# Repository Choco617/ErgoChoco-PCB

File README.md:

# ErgoChoco-PCB
 My first PCB - a de-split split layout taking my favorite design details from the Corne, Kyria, Absolem, and others.

## The name
 I'm an engineer, and true to form I'm bad at naming things. I'd heard the ErgoDox was designed by a user named Dox, and my handle is Choco617, so: ErgoChoco.
 
## Layout explanation:
I love my Corne, but I quickly found that I always orient the halves the same way, making the actual separation and the TRRS cable more of a nuisance, much as I love the concept. So I experimented with angles and settled on 30°. I had also always wondered if I would like more columnar stagger: the Corne seems pretty conservative on that. So after reading the Kyria design log, I took the same approach, made some measurements of my own fingers’ natural resting positions, and discovered they were negligibly different from the Kyria’s, so I lifted those columnar stagger dimensions wholesale. I love the look of the 1.5U thumb keys on the Corne, but I admit it’s always been annoying for keycap compatibility that they prevent me from just getting a Planck set, so I replaced the 1.5U keys with 1U. I set the hands just far enough apart to fit a Pro Micro between them. A cardboard prototype with leftover switches/caps stuffed into it confirmed that was a comfy layout for me (and the all-1U thumb arcs don’t look as bad as I worried they would).

## Design Priorities:

### PCB
- Kailh hotswap sockets (direct soldering not supported: I'm the only intended user, so I can do what I want :P)
- In-switch LED (with Holtites so that it doesn't defeat the purpose of switch hotswap)
- South-facing switches (I like seeing the LEDs right up front)
- Pro Micro. I originally designed this with an onboard MCU, then decided I would rather keep all the complicated stuff on a Pro Micro to keep the PCB simpler/cheaper and allow me to replace the controller if something awful happened. Also, Pro Micro instead of Elite-C just because I already have micro-USB cables. The Pro Micro is socketed anyway, so I can always change later if I feel like it.
- SMD all the things (mostly diodes/resistors). I wanted to see if I could actually solder all of it myself, and I like the idea of keeping everything as small as possible, and technically minimizing EMI.
- Ground plane everywhere. My original Contra was very prone to ESD shocks, so in the original onboard-MCU version of this PCB, I had an ESD protection circuit with a PRTR5V0U2X. Now with a Pro Micro design, the best I can do (I think) is extensive ground planes and connecting the mounting holes to them so the PCB is grounded to the stainless steel case. I'm a mechanical engineer, not an electrical engineer, so I hope this is sufficient.
- Breakout pads for GND/+5V/F4 data pin to allow RGB underglow (inspired by the Contra). Not sure where I would physically fit an RGB strip, since I intentionally designed no gap under the PCB, but it seemed silly not to include this while I was designing the PCB, since I had the pin available.

### Case (dedicated repo: [https://github.com/Choco617/ErgoChoco-case](https://github.com/Choco617/ErgoChoco-case))
- Stainless sandwich/skeleton case. Top and bottom plates have a perimeter of 8mm aluminum standoffs around the edges of the PCB. I've used this in previous boards, and I love the look.
- Bottom plate mechanically supports hotswap sockets from behind. It annoys me that switch-swapping in my sandwich-case Corne requires me to disassemble everything so I can hold the sockets firm when I insert the new switches, so this case is designed so that the bottom plate (through a layer of non-conductive gasket) contacts the sockets. The PCB is bolted to the bottom plate to keep this secure.
- Minimal height. Without resorting to low-profile switches, I want to keep the plate height as low as possible, mainly for aesthetics and comfort reasons, but also because it's mechanically necessary in order to let the bottom plate contact the backs of the hotswap sockets.
- Pro Micro installation on PCB: to minimize height but still keep the Pro Micro under the plate (I don't like them exposed like on the Corne), the PCB has a U-shaped relief at the Pro Micro footprint. The Pro Micro is installed component-side down on the top of the PCB so the USB port hangs down into that relief.
- Case structure as a result of these choices: PCB is bolted to the top of the bottom plate, with a gasket layer (just vaguely compressible rubbery drawer liner, nothing fancy) in between for electrical insulation, then standoffs are bolted to the top of the bottom plate around the PCB, then the top plate is bolted to the standoffs, then switches are inserted.

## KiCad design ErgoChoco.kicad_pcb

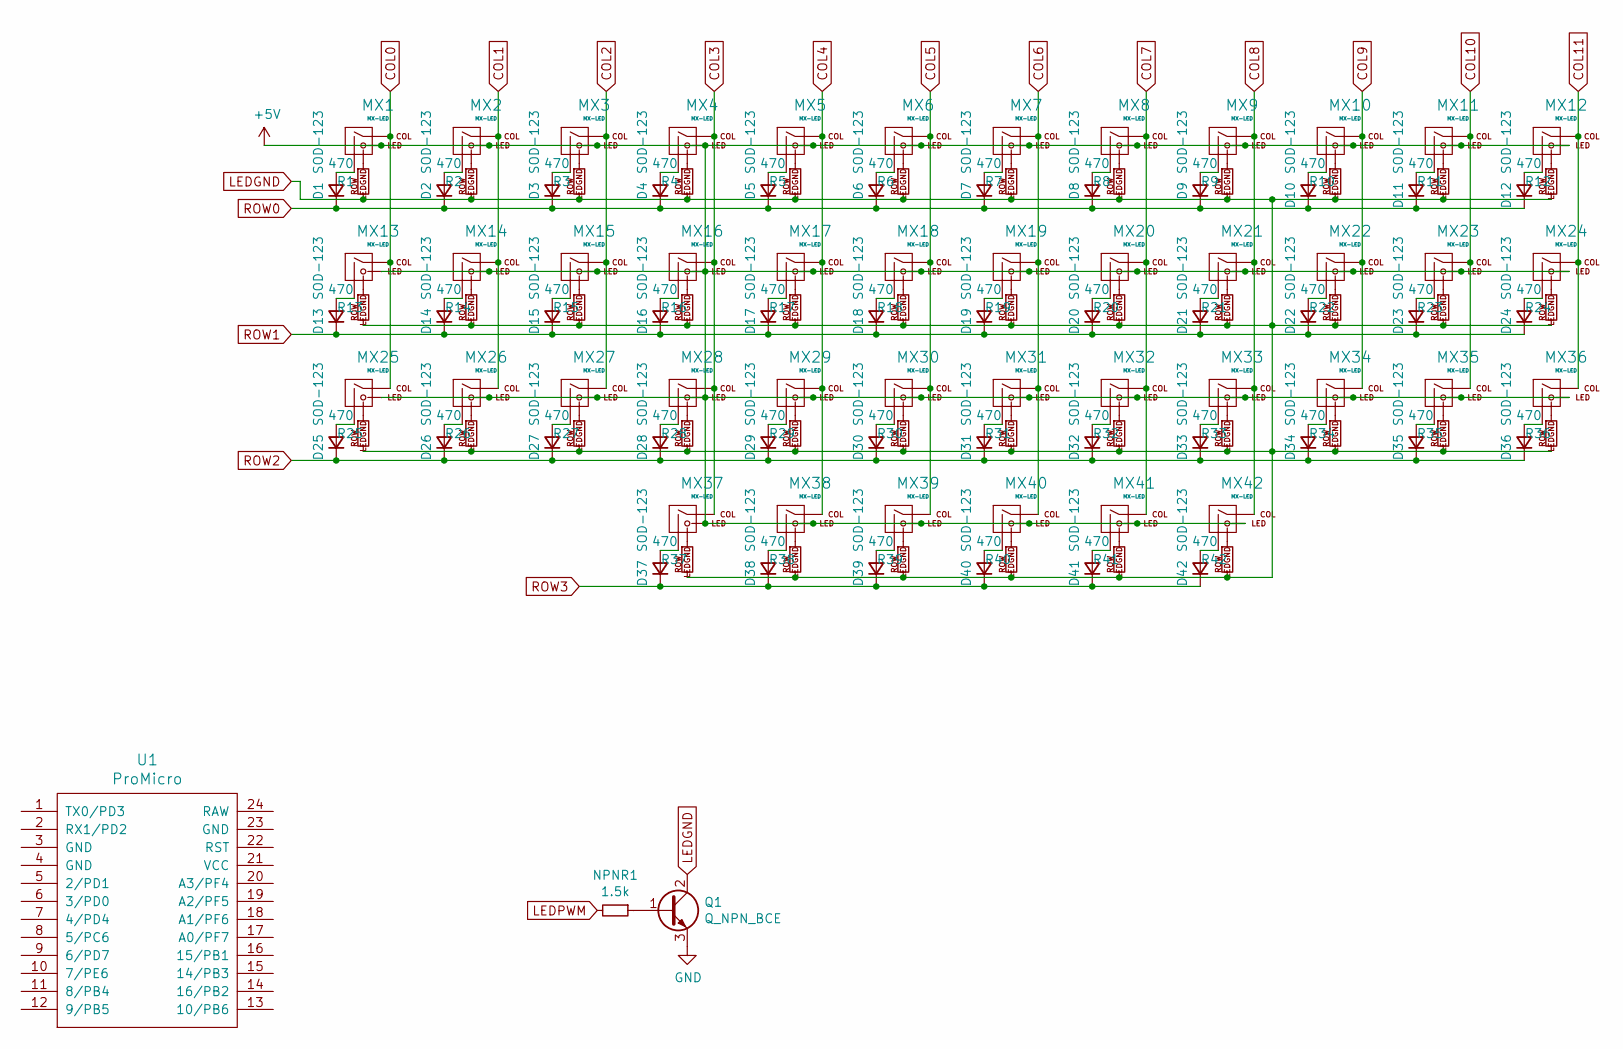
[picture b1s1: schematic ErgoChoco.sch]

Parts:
D1, D2, D3, D4, D5, D6, D7, D8, D9, D10, D11, D12, D13, D14, D15, D16, D17, D18, D19, D20, D21, D22, D23, D24, D25, D26, D27, D28, D29, D30, D31, D32, D33, D34, D35, D36, D37, D38, D39, D40, D41, D42: SOD-123; D_SOD-123-HandSolder
MX1, MX2, MX3, MX4, MX5, MX6, MX7, MX8, MX9, MX10, MX11, MX12, MX13, MX14, MX15, MX16, MX17, MX18, MX19, MX20, MX21, MX22, MX23, MX24, MX25, MX26, MX27, MX28, MX29, MX30, MX31, MX32, MX33, MX34, MX35, MX36, MX37, MX38, MX39, MX40, MX41, MX42: MX-LED; Kailh_socket_MX_PCBmount_LED_1U
NPNR1: 1.5k; R_0805_2012Metric
Q1: Q_NPN_BCE; Trans_SOT-223-4
R1, R2, R3, R4, R5, R6, R7, R8, R9, R10, R11, R12, R13, R14, R15, R16, R17, R18, R19, R20, R21, R22, R23, R24, R25, R26, R27, R28, R29, R30, R31, R32, R33, R34, R35, R36, R37, R38, R39, R40, R41, R42: 470; R_0805_2012Metric
U1: ProMicro; ArduinoProMicro

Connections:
+5V: MX1.3 (LED), MX2.3 (LED), MX3.3 (LED), MX4.3 (LED), MX5.3 (LED), MX6.3 (LED), MX7.3 (LED), MX8.3 (LED), MX9.3 (LED), MX10.3 (LED), MX11.3 (LED), MX12.3 (LED), MX13.3 (LED), MX14.3 (LED), MX15.3 (LED), MX16.3 (LED), MX17.3 (LED), MX18.3 (LED), MX19.3 (LED), MX20.3 (LED), MX21.3 (LED), MX22.3 (LED), MX23.3 (LED), MX24.3 (LED), MX25.3 (LED), MX26.3 (LED), MX27.3 (LED), MX28.3 (LED), MX29.3 (LED), MX30.3 (LED), MX31.3 (LED), MX32.3 (LED), MX33.3 (LED), MX34.3 (LED), MX35.3 (LED), MX36.3 (LED), MX37.3 (LED), MX38.3 (LED), MX39.3 (LED), MX40.3 (LED), MX41.3 (LED), MX42.3 (LED), U1.21 (VCC); also elsewhere on the board
COL0: MX1.1 (COL), MX13.1 (COL), MX25.1 (COL), U1.19 (A2/PF5)
COL1: MX2.1 (COL), MX14.1 (COL), MX26.1 (COL), U1.18 (A1/PF6)
COL2: MX3.1 (COL), MX15.1 (COL), MX27.1 (COL), U1.17 (A0/PF7)
COL3: MX4.1 (COL), MX16.1 (COL), MX28.1 (COL), MX37.1 (COL), U1.16 (15/PB1)
COL4: MX5.1 (COL), MX17.1 (COL), MX29.1 (COL), MX38.1 (COL), U1.15 (14/PB3)
COL5: MX6.1 (COL), MX18.1 (COL), MX30.1 (COL), MX39.1 (COL), U1.14 (16/PB2)
COL6: MX7.1 (COL), MX19.1 (COL), MX31.1 (COL), MX40.1 (COL), U1.8 (5/PC6)
COL7: MX8.1 (COL), MX20.1 (COL), MX32.1 (COL), MX41.1 (COL), U1.7 (4/PD4)
COL8: MX9.1 (COL), MX21.1 (COL), MX33.1 (COL), MX42.1 (COL), U1.6 (3/PD0)
COL9: MX10.1 (COL), MX22.1 (COL), MX34.1 (COL), U1.5 (2/PD1)
COL10: MX11.1 (COL), MX23.1 (COL), MX35.1 (COL), U1.2 (RX1/PD2)
COL11: MX12.1 (COL), MX24.1 (COL), MX36.1 (COL), U1.1 (TX0/PD3)
GND: Q1.3 (E), U1.3 (GND), U1.4 (GND), U1.23 (GND); also elsewhere on the board
LEDGND: Q1.2 (C), R1.2, R2.2, R3.2, R4.2, R5.2, R6.2, R7.2, R8.2, R9.2, R10.2, R11.2, R12.2, R13.2, R14.2, R15.2, R16.2, R17.2, R18.2, R19.2, R20.2, R21.2, R22.2, R23.2, R24.2, R25.2, R26.2, R27.2, R28.2, R29.2, R30.2, R31.2, R32.2, R33.2, R34.2, R35.2, R36.2, R37.2, R38.2, R39.2, R40.2, R41.2, R42.2
LEDPWM: NPNR1.2, U1.12 (9/PB5)
unnamed: D1.2 (A), MX1.2 (ROW)
unnamed: D2.2 (A), MX2.2 (ROW)
unnamed: D3.2 (A), MX3.2 (ROW)
unnamed: D4.2 (A), MX4.2 (ROW)
unnamed: D5.2 (A), MX5.2 (ROW)
unnamed: D6.2 (A), MX6.2 (ROW)
unnamed: D7.2 (A), MX7.2 (ROW)
unnamed: D8.2 (A), MX8.2 (ROW)
unnamed: D9.2 (A), MX9.2 (ROW)
unnamed: D10.2 (A), MX10.2 (ROW)
unnamed: D11.2 (A), MX11.2 (ROW)
unnamed: D12.2 (A), MX12.2 (ROW)
unnamed: D13.2 (A), MX13.2 (ROW)
unnamed: D14.2 (A), MX14.2 (ROW)
unnamed: D15.2 (A), MX15.2 (ROW)
unnamed: D16.2 (A), MX16.2 (ROW)
unnamed: D17.2 (A), MX17.2 (ROW)
unnamed: D18.2 (A), MX18.2 (ROW)
unnamed: D19.2 (A), MX19.2 (ROW)
unnamed: D20.2 (A), MX20.2 (ROW)
unnamed: D21.2 (A), MX21.2 (ROW)
unnamed: D22.2 (A), MX22.2 (ROW)
unnamed: D23.2 (A), MX23.2 (ROW)
unnamed: D24.2 (A), MX24.2 (ROW)
unnamed: D25.2 (A), MX25.2 (ROW)
unnamed: D26.2 (A), MX26.2 (ROW)
unnamed: D27.2 (A), MX27.2 (ROW)
unnamed: D28.2 (A), MX28.2 (ROW)
unnamed: D29.2 (A), MX29.2 (ROW)
unnamed: D30.2 (A), MX30.2 (ROW)
unnamed: D31.2 (A), MX31.2 (ROW)
unnamed: D32.2 (A), MX32.2 (ROW)
unnamed: D33.2 (A), MX33.2 (ROW)
unnamed: D34.2 (A), MX34.2 (ROW)
unnamed: D35.2 (A), MX35.2 (ROW)
unnamed: D36.2 (A), MX36.2 (ROW)
unnamed: D37.2 (A), MX37.2 (ROW)
unnamed: D38.2 (A), MX38.2 (ROW)
unnamed: D39.2 (A), MX39.2 (ROW)
unnamed: D40.2 (A), MX40.2 (ROW)
unnamed: D41.2 (A), MX41.2 (ROW)
unnamed: D42.2 (A), MX42.2 (ROW)
unnamed 58: U1.20 (A3/PF4); also elsewhere on the board
unnamed: MX1.4 (LEDGND), R1.1
unnamed: MX2.4 (LEDGND), R2.1
unnamed: MX3.4 (LEDGND), R3.1
unnamed: MX4.4 (LEDGND), R4.1
unnamed: MX5.4 (LEDGND), R5.1
unnamed: MX6.4 (LEDGND), R6.1
unnamed: MX7.4 (LEDGND), R7.1
unnamed: MX8.4 (LEDGND), R8.1
unnamed: MX9.4 (LEDGND), R9.1
unnamed: MX10.4 (LEDGND), R10.1
unnamed: MX11.4 (LEDGND), R11.1
unnamed: MX12.4 (LEDGND), R12.1
unnamed: MX13.4 (LEDGND), R13.1
unnamed: MX14.4 (LEDGND), R14.1
unnamed: MX15.4 (LEDGND), R15.1
unnamed: MX16.4 (LEDGND), R16.1
unnamed: MX17.4 (LEDGND), R17.1
unnamed: MX18.4 (LEDGND), R18.1
unnamed: MX19.4 (LEDGND), R19.1
unnamed: MX20.4 (LEDGND), R20.1
unnamed: MX21.4 (LEDGND), R21.1
unnamed: MX22.4 (LEDGND), R22.1
unnamed: MX23.4 (LEDGND), R23.1
unnamed: MX24.4 (LEDGND), R24.1
unnamed: MX25.4 (LEDGND), R25.1
unnamed: MX26.4 (LEDGND), R26.1
unnamed: MX27.4 (LEDGND), R27.1
unnamed: MX28.4 (LEDGND), R28.1
unnamed: MX29.4 (LEDGND), R29.1
unnamed: MX30.4 (LEDGND), R30.1
unnamed: MX31.4 (LEDGND), R31.1
unnamed: MX32.4 (LEDGND), R32.1
unnamed: MX33.4 (LEDGND), R33.1
unnamed: MX34.4 (LEDGND), R34.1
unnamed: MX35.4 (LEDGND), R35.1
unnamed: MX36.4 (LEDGND), R36.1
unnamed: MX37.4 (LEDGND), R37.1
unnamed: MX38.4 (LEDGND), R38.1
unnamed: MX39.4 (LEDGND), R39.1
unnamed: MX40.4 (LEDGND), R40.1
unnamed: MX41.4 (LEDGND), R41.1
unnamed: MX42.4 (LEDGND), R42.1
unnamed: NPNR1.1, Q1.1 (B)
unnamed 102: U1.22 (RST); also elsewhere on the board
ROW0: D1.1 (K), D2.1 (K), D3.1 (K), D4.1 (K), D5.1 (K), D6.1 (K), D7.1 (K), D8.1 (K), D9.1 (K), D10.1 (K), D11.1 (K), D12.1 (K), U1.9 (6/PD7)
ROW1: D13.1 (K), D14.1 (K), D15.1 (K), D16.1 (K), D17.1 (K), D18.1 (K), D19.1 (K), D20.1 (K), D21.1 (K), D22.1 (K), D23.1 (K), D24.1 (K), U1.10 (7/PE6)
ROW2: D25.1 (K), D26.1 (K), D27.1 (K), D28.1 (K), D29.1 (K), D30.1 (K), D31.1 (K), D32.1 (K), D33.1 (K), D34.1 (K), D35.1 (K), D36.1 (K), U1.11 (8/PB4)
ROW3: D37.1 (K), D38.1 (K), D39.1 (K), D40.1 (K), D41.1 (K), D42.1 (K), U1.13 (10/PB6)

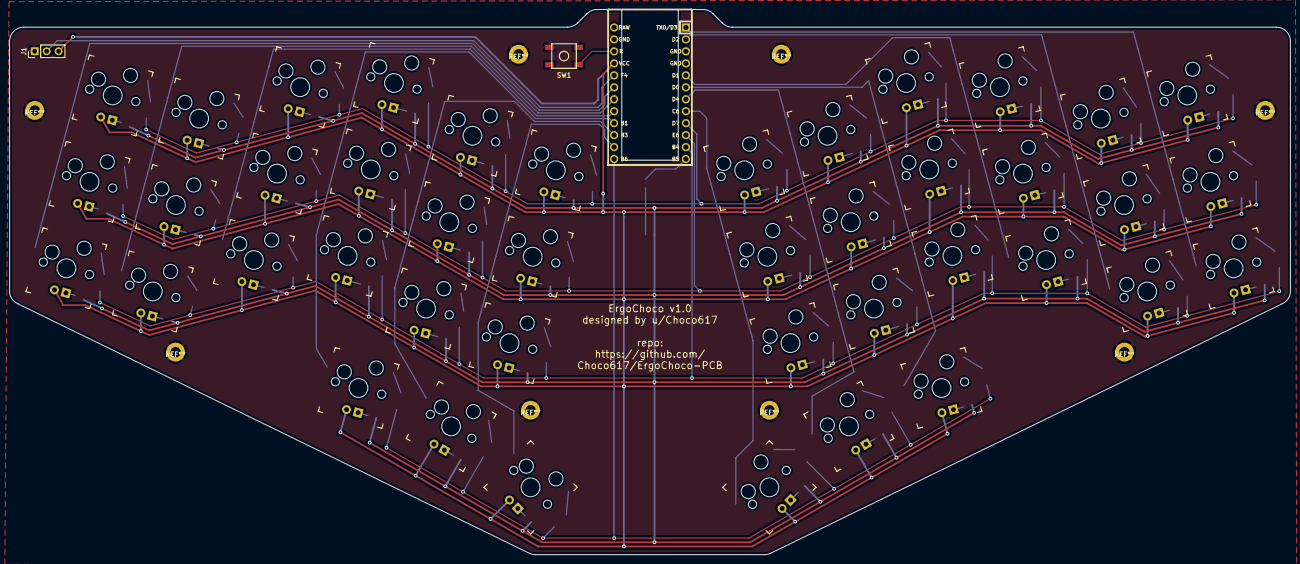
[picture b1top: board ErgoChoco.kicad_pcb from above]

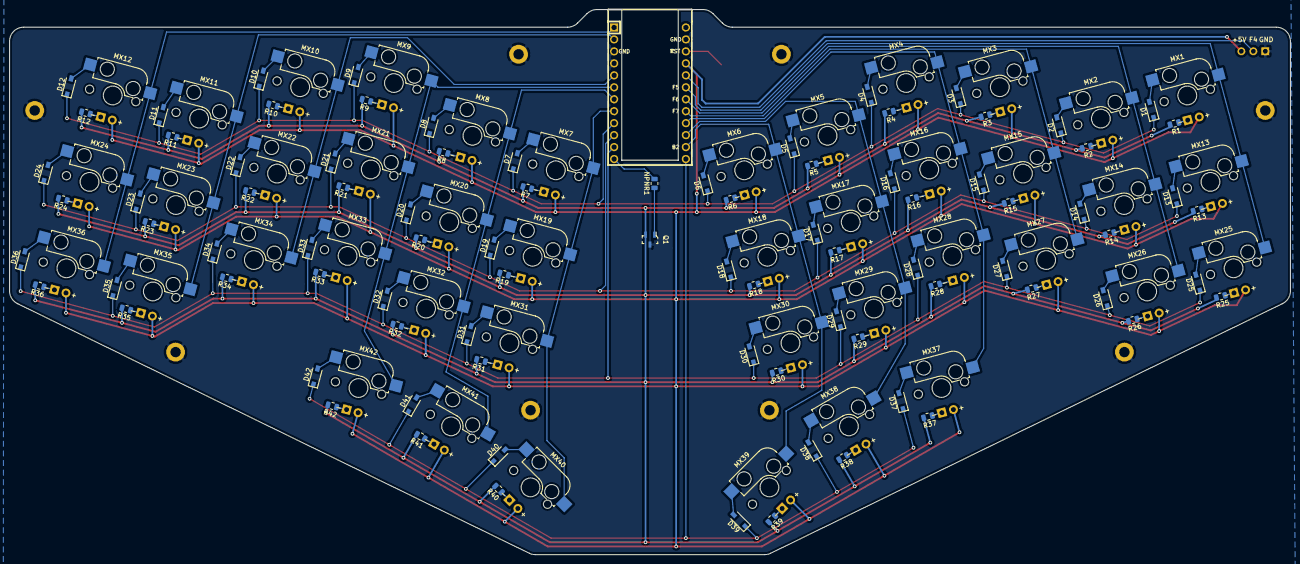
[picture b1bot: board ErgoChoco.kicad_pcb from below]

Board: 2 copper layers, 272.0 x 115.8 mm, 131 parts (87 on the bottom side), 107 nets.

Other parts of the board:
J1: Conn_01x03; PinHeader_1x03_P2.54mm_Vertical
SW1: SW_Push; SKQG-1155865

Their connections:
+5V: J1.3; also elsewhere on the board
GND: J1.1, SW1.2; also elsewhere on the board
unnamed 58: J1.2; also elsewhere on the board
unnamed 102: SW1.1; also elsewhere on the board

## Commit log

2020-06-16 initialize KiCAD project
    literally just making a new blank project
2020-06-16 added ai03's submodules
2020-06-16 added libraries
2020-06-16 schematic done-ish
    still to do (at least):
    assign real reference designators to everything (number switches, diodes, resistors, etc.)
    assign rows/columns to specific pins on the atmega32u4 (will do this based on convenient routing in the pcb layout, so I don't know yet)
    add something for ESD protection probably
    probably some other stuff I haven't thought of yet
2020-06-16 LED PWM
    immediately thought of a schematic update to make: LED PWM
2020-06-16 USB resistors
    another schematic update to add resistors to USB D+/-
2020-06-16 add daprice submodule for Kailh hotswap reference footprint
2020-06-18 created footprints
    new footprints combining Kailh hotswap sockets and LEDs
2020-06-18 added PCB mount holes to custom footprints
2020-06-19 assigned reference designators
2020-06-19 add Digi-Key KiCad library for micro USB footprint
2020-06-19 add manufacturer USB footprint, renumber resistors
    Realized I had R1-R6 but also my LED resistors were numbered in sync with the switches, so 1-6 were doubled up. Renumbered 1-6 to 43-48. Also, I found that the micro USB port manufacturer offers thei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
2020-06-19 added ESD
    added ESD IC used in Masterzen's PCB design guide, the CPM43, and the Voyager40
2020-06-20 remove redundant USB resistors, add submodule for JLCPCB design rules
2020-06-20 PCB layout setup
    imported JLCPCB design rules from sethhillbrand, set some settings per ai03's guide, about to import everything and start doing layout
2020-06-20 imported schematic and vaguely located switches
2020-06-20 vaguely located MCU related components
2020-06-21 precisely located all switches
    switches, diodes, and LED resistors located by coordinates generated from mechanical CAD layout
2020-06-22 MCU components better placed
    moved MCU components around atmega32u4 as needed, moved whole group to center, moved MOSFET to right hand gap under period, moved reset switch to left hand under X
2020-06-22 added edge cuts
    -corrected layer settings
    -made net class settings
    -added edge cuts
    -located MCU components pretty precisely
    -located micro USB precisely
    -started routing
2020-06-23 more MCU routing
2020-06-23 routed all switches to their diodes
    also some column 0 stuff
2020-06-23 routed switch rows and columns
2020-06-24 routed LEDGND and the missed bottom switch row
2020-06-24 routed more LED stuff
    -routed LED +5V
    -removed unnecessary traces between hands (just because I relied on LED rows in the handwire doesn't mean I have to on this PCB)
    -routed all LEDs to their respective resistors
2020-06-25 replaced MOSFET footprint, started routing right hand columns
2020-06-28 routed rows and columns
2020-06-28 added mounting holes
2020-06-28 routed decoupling capacitors 5V
    -also swapped 10uF cap with one of the 0.1uF ones to put the 10 in the correct place
    -about to rotate the whole MCU region 180 degrees to correct a USB routing sin, this is going to involve rerouting all the row/column connections to the MCU but probably result in tidier traces overa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
2020-06-28 rotated MCU region and routed rows
2020-07-04 rerouted columns
2020-07-05 add ground fills, adjust some traces to improve clearance
2020-07-05 added tooling holes
2020-07-05 added name/rev/repo details on silkscreen layer
2020-07-05 renamed KiCad project from Corneus to ErgoChoco
2020-07-05 update titleblocks on schematic and pcb layout
    -license updated from MIT to CC BY-NC
    -project name updated in titleblock
    -date updated to 7.5.20
2020-07-13 late updates before asking Reddit for help
    -remove tooling holes again
    -rename BOM and add JLCPCB BOM + CPL
    -update readme to include layout explanation
    -add gerbers
2020-07-13 add schematic PCB, update readme, remove DXFs
2020-07-13 started deleting things from integrated MCU
    -deleted traces and edge cuts in pcbnew
2020-07-13 Add keebio library for Pro Micro stuff
2020-07-13 deleted old schematic for atmega32u4 also
2020-07-13 Add Keebio schematic symbols
2020-07-13 introduced Pro Micro
    -put Pro Micro into schematic
    -updated PCB from schematic
    -moved all switches 10mm farther apart
2020-07-14 routed columns
    -routed columns together (not to Pro Micro yet)
    -flipped diodes and resistors to back side of board
    -added calculator for figuring out weird angles of traces
2020-07-14 routed LH top row
2020-07-15 routed other two LH rows
    -still excluding innermost row and thumb cluster for now
2020-07-16 routed right hand and thumb arcs
    -still haven't routed innermost column on left hand
    -need to establish Pro Micro location and edge cuts first
2020-07-16 added edge cuts, located PM
2020-07-26 finished routing, added mounting holes
2020-07-26 Update LICENSE to CC BY-NC
2020-07-26 update README to explain design
2021-10-30 update README to link to case repo
2021-11-22 updated BOM csvs for Pro Micro version
    -deleted JLCPCB csvs
    -revised detailed BOM to show components I actually used

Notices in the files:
ErgoChoco.kicad_pcb:
License: CC BY-NC
